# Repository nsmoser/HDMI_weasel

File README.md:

This board exists to switch between a pass-through HDMI signal and an HDMI signal generated from an RP2350A chip.
Note that this board does not contain HDMI connectors, but it does have FFC connectors for routing HDMI signals on/off board.
Has some DIP mechanical interfaces for working the chip, and an FFC connector w/ SPI & I2C pinned out for an add-on board.
Micro-SD card connector on the back to source images for the generated HDMI signal.

This was originally intended as a prank device (ex. take a screenshot of your neighbor's PC, load it on the SD card, and switch the input),
but it could also see use as a digital meeting or menu board on a single-input display where frequent switching between display on a loop and
a presentation from an external HDMI source.

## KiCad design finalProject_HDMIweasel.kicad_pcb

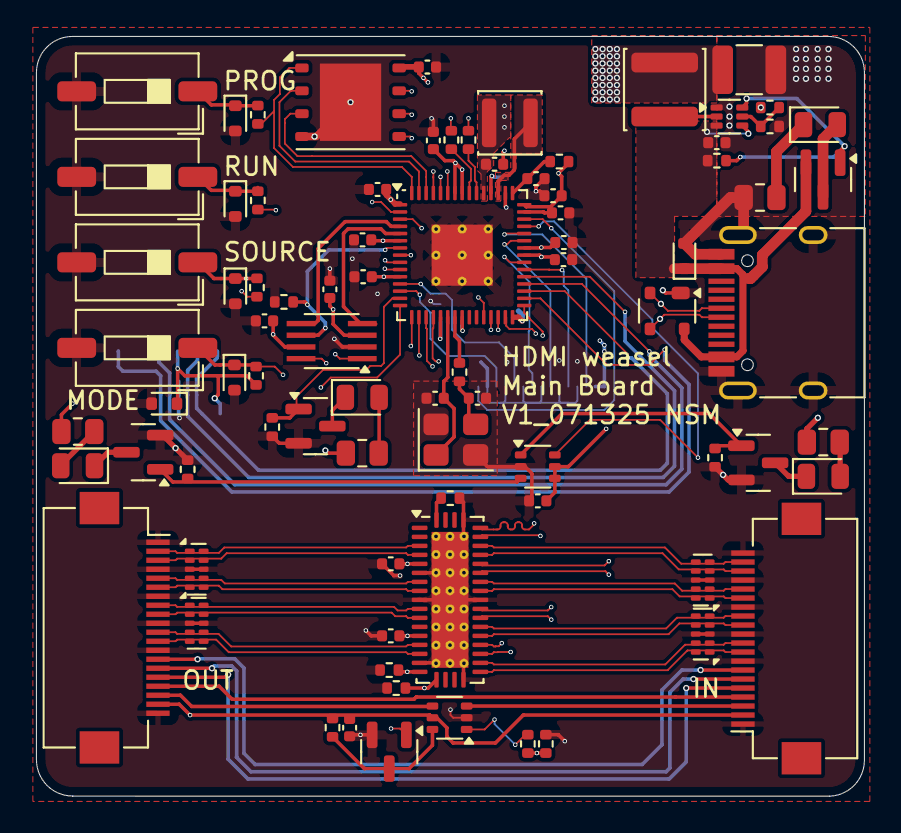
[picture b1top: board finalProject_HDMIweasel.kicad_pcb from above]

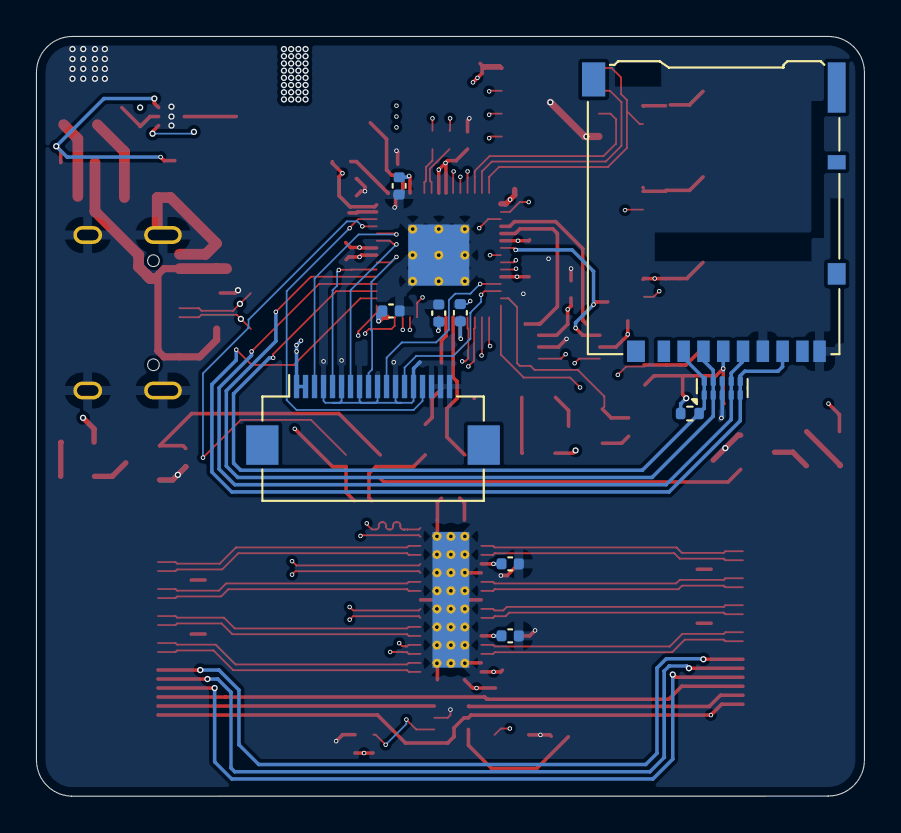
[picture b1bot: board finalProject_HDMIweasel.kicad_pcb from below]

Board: 6 copper layers, 46.0 x 42.2 mm, 93 parts (10 on the bottom side), 90 nets.

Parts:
C001, C201, C202, C203, C204, C205: 0.1u; C_0402_1005Metric
C101: 2.2u; C_0402_1005Metric
C102: 47u; C_1210_3225Metric
C301, C302, C303, C314: 4.7u; C_0402_1005Metric
C304, C305, C306, C307, C308, C309, C310, C311, C312, C313, C315, C318, C319: 100n; C_0402_1005Metric
C316, C317: 15p; C_0402_1005Metric
D001, D002, D003, D103: LED; LED_0805_2012Metric
D101: ESD5Z5V0; D_SOD-523
D102: PRTR5V0U2X; SOT-143
D301, D302, D303, D304, D305: ESD5Z3V3; D_SOD-523
J001: Conn_01x18_Pin; Hirose_FH12-18S-0.5SH_1x18-1MP_P0.50mm_Horizontal
J201, J202: Conn_01x20_Pin; Hirose_FH12-20S-0.5SH_1x20-1MP_P0.50mm_Horizontal
J301: Micro_SD_Card; microSD_HC_Hirose_DM3AT-SF-PEJM5
L101: 1u; L_Sunlord_SWPA4030S
L301: 3.3u; L_Sunlord_SWPA3015S
P101: USB_C_Plug_USB2.0; USB_C_Receptacle_HRO_TYPE-C-31-M-12
Q001, Q002, Q003, Q201: BSS138; SOT-23
Q101: BSS83P; SOT-23
R001, R003, R005, R102, R103, R204, R309, R310: 100k; R_0402_1005Metric
R002: 22; R_0805_2012Metric
R004, R006: 42.2; R_0805_2012Metric
R101: 453k; R_0402_1005Metric
R104: 188; R_0805_2012Metric
R201, R202, R203, R305, R306, R311: 10k; R_0402_1005Metric
R301, R302: 27; R_0402_1005Metric
R303, R304: 1k; R_0402_1005Metric
R307, R308: 100K; R_0402_1005Metric
R312: 33; R_0402_1005Metric
SW301, SW302, SW304, SW305: SW_DIP_x01; SW_DIP_SPSTx01_Slide_6.7x4.1mm_W6.73mm_P2.54mm_LowProfile_J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
U001, U206: TS5A3159ADCK; SOT-363_SC-70-6
U101: TPS62A02ADRL; SOT-563
U201: TMUXHS4412; WQFN-42-1EP_3.5x9mm_P0.5mm_EP2.05x7.55mm_ThermalVias
U202, U203, U204, U205, U304: TPD4E02B04DQA; USON-10_2.5x1.0mm_P0.5mm
U301: RP2350; QFN-60-1EP_7x7mm_P0.4mm_EP3.4x3.4mm_ThermalVias
U302: W25Q128JVP; WSON-8-1EP_6x5mm_P1.27mm_EP3.4x4.3mm
U303: TXS0102DCT; SSOP-8_2.95x2.8mm_P0.65mm
Y1: ABM8-22272-T3; Crystal_SMD_3225-4Pin_3.2x2.5mm

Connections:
+1V1: C302.1, C312.1, C313.1, C314.1, L301.1, U301.6 (DVDD), U301.23 (DVDD), U301.39 (DVDD), U301.50 (VREG_FB)
+3.3V: C001.1, C102.1, C201.1, C202.1, C203.1, C204.1, C303.1, C304.1, C305.1, C306.1, C307.1, C308.1, C309.1, C310.1, C311.1, C315.1, C319.1, D305.1 (K), J001.1, J001.2, J301.4 (VDD), L101.2, R002.1, R004.1, R006.1, R101.1, R309.1, R310.1, R311.2, R312.2, U001.4, U001.5 (V+), U201.5 (VCC), U201.13 (VCC), U301.1 (IOVDD), U301.11 (IOVDD), U301.20 (IOVDD), U301.30 (IOVDD), U301.38 (IOVDD), U301.44 (ADC_AVDD), U301.45 (IOVDD), U301.49 (VREG_VIN), U301.53 (USB_OTP_VDD), U301.54 (QSPI_IOVDD), U302.8 (VCC), U303.3 (VCCA)
/HDMI_switch/CEC: J201.14, J202.7, U301.15 (GPIO11)
/HDMI_switch/HDMI_IN_CK+: J202.19, U201.36 (DB0P), U205.5 (IO4)
/HDMI_switch/HDMI_IN_CK-: J202.18, U201.35 (DB0N), U205.4 (IO3)
/HDMI_switch/HDMI_IN_D0+: J202.16, U201.32 (DB1P), U205.2 (IO2)
/HDMI_switch/HDMI_IN_D0-: J202.15, U201.31 (DB1N), U205.1 (IO1)
/HDMI_switch/HDMI_IN_D1+: J202.13, U201.27 (DB2P), U204.5 (IO4)
/HDMI_switch/HDMI_IN_D1-: J202.12, U201.26 (DB2N), U204.4 (IO3)
/HDMI_switch/HDMI_IN_D2+: J202.10, U201.23 (DB3P), U204.2 (IO2)
/HDMI_switch/HDMI_IN_D2-: J202.9, U201.22 (DB3N), U204.1 (IO1)
/HDMI_switch/HDMI_OUT_CLK+: J201.2, U201.3 (D0P), U203.1 (IO1)
/HDMI_switch/HDMI_OUT_CLK-: J201.3, U201.4 (D0N), U203.2 (IO2)
/HDMI_switch/HDMI_OUT_D0+: J201.5, U201.7 (D1P), U203.4 (IO3)
/HDMI_switch/HDMI_OUT_D0-: J201.6, U201.8 (D1N), U203.5 (IO4)
/HDMI_switch/HDMI_OUT_D1+: J201.8, U201.10 (D2P), U202.1 (IO1)
/HDMI_switch/HDMI_OUT_D1-: J201.9, U201.11 (D2N), U202.2 (IO2)
/HDMI_switch/HDMI_OUT_D2+: J201.11, U201.14 (D3P), U202.4 (IO3)
/HDMI_switch/HDMI_OUT_D2-: J201.12, U201.15 (D3N), U202.5 (IO4)
/HDMI_switch/HOTPLUG_OUT: J201.18, U206.4
/HDMI_switch/PD: R201.1, U201.18 (PD), U301.3 (GPIO1)
/HDMI_switch/RPI_CLK+: U201.38 (DA0P), U301.18 (GPIO14)
/HDMI_switch/RPI_CLK-: U201.37 (DA0N), U301.19 (GPIO15)
/HDMI_switch/RPI_D0+: U201.34 (DA1P), U301.29 (GPIO18)
/HDMI_switch/RPI_D0-: U201.33 (DA1N), U301.31 (GPIO19)
/HDMI_switch/RPI_D1+: U201.29 (DA2P), U301.27 (GPIO16)
/HDMI_switch/RPI_D1-: U201.28 (DA2N), U301.28 (GPIO17)
/HDMI_switch/RPI_D2+: U201.25 (DA3P), U301.16 (GPIO12)
/HDMI_switch/RPI_D2-: U201.24 (DA3N), U301.17 (GPIO13)
/HDMI_switch/RPI_HOTPLUG: R307.2, U206.1
/HDMI_switch/SCL: J201.15, J202.6, U303.1 (B2)
/HDMI_switch/SDA: J201.16, J202.5, U303.8 (B1)
/HDMI_switch/SEL: Q201.1 (G), R202.1, U201.17 (SEL), U301.2 (GPIO0)
/HDMI_switch/V_HDMI: C205.1, C318.1, J201.19, J202.2, R204.1, U206.5 (V+), U303.7 (VCCB)
/HDMI_switch/hotplug: J202.3, U206.3
/HDMI_switch/util: J201.17, J202.4
/Microcontroller/HDMI_COMM_EN: R306.2, U301.7 (GPIO4), U303.6 (OE)
/Microcontroller/LED_HDMISOURCE: U001.6, U301.42 (GPIO28_ADC2)
/Microcontroller/LED_SYSACTIVE: Q001.1 (G), R001.1, U301.14 (GPIO10)
/Microcontroller/MANUAL_SWITCH: D303.1 (K), R309.2, SW304.1, U301.9 (GPIO6)
/Microcontroller/MODE_SWITCH: D304.1 (K), R310.2, SW305.1, U301.10 (GPIO7)
/Microcontroller/QSPI_SS: R303.2, U301.60 (QSPI_SS), U302.1 (~CS)
/Microcontroller/RPI_ADC (GPIO29): J001.15, U301.43 (GPIO29_ADC3)
/Microcontroller/RPI_SCL0 (GPIO9): J001.13, U301.13 (GPIO9)
/Microcontroller/RPI_SCL1: U301.5 (GPIO3), U303.4 (A2)
/Microcontroller/RPI_SDA0 (GPIO8): J001.11, U301.12 (GPIO8)
/Microcontroller/RPI_SDA1: U301.4 (GPIO2), U303.5 (A1)
/Microcontroller/RPI_SPI1_CS0 (GPIO25): J001.9, U301.37 (GPIO25)
/Microcontroller/RPI_SPI1_RX (GPIO24): J001.5, U301.36 (GPIO24)
/Microcontroller/RPI_SPI1_SCK (GPIO26): J001.7, U301.40 (GPIO26_ADC0)
/Microcontroller/RPI_SPI1_TX (GPIO27): J001.3, U301.41 (GPIO27_ADC1)
/Microcontroller/SPI0_CS0: J301.2 (DAT3/CD), R311.1, U301.33 (GPIO21), U304.1 (IO1)
/Microcontroller/SPI0_RX: J301.7 (DAT0), U301.32 (GPIO20), U304.5 (IO4)
/Microcontroller/SPI0_SCK: J301.5 (CLK), U301.34 (GPIO22), U304.4 (IO3)
/Microcontroller/SPI0_TX: J301.3 (CMD), U301.35 (GPIO23), U304.2 (IO2)
/Microcontroller/USB_D1N: R301.1, U301.51 (USB_DN)
/Microcontroller/USB_D1P: R302.1, U301.52 (USB_DP)
/Microcontroller/USB_DN: D102.2 (I/O1), P101.A7 (D-), R301.2
/Microcontroller/USB_DP: D102.3 (I/O2), P101.A6 (D+), R302.2
/Microcontroller/VREG_LX: L301.2, U301.48 (VREG_LX)
GND: C001.2, C101.2, C102.2, C201.2, C202.2, C203.2, C204.2, C205.2, C301.2, C302.2, C303.2, C304.2, C305.2, C306.2, C307.2, C308.2, C309.2, C310.2, C311.2, C312.2, C313.2, C314.2, C315.2, C316.2, C317.2, C318.2, C319.2, D101.2 (A), D102.1 (GND), D301.2 (A), D302.2 (A), D303.2 (A), D304.2 (A), D305.2 (A), J001.4, J001.6, J001.8, J001.10, J001.12, J001.14, J001.16, J001.17, J001.18, J201.1, J201.4, J201.7, J201.10, J201.13, J201.20, J202.1, J202.8, J202.11, J202.14, J202.17, J202.20, J301.6 (VSS), J301.9 (SHIELD), P101.A1 (GND), P101.A12 (GND), P101.B1 (GND), P101.B12 (GND), P101.S1 (SHIELD), Q001.2 (S), Q002.2 (S), Q003.2 (S), Q201.2 (S), R001.2, R003.2, R005.2, R102.2, R104.2, R201.2, R202.2, R203.1, R306.1, R308.2, SW301.2, SW302.2, SW304.2, SW305.2, U001.2 (GND), U101.1 (GND), U201.6 (GND), U201.9 (GND), U201.16 (GND), U201.21 (GND), U201.30 (GND), U201.39 (GND), U201.43 (GND), U202.3 (G), U202.8 (G), U203.3 (G), U203.8 (G), U204.3 (G), U204.8 (G), U205.3 (G), U205.8 (G), U206.2 (GND), U301.47 (VREG_PGND), U301.61 (GND), U302.4 (GND), U302.9 (EP), U303.2 (GND), U304.3 (G), U304.8 (G), Y1.2, Y1.4
unnamed: C316.1, R304.1, Y1.3
unnamed: D001.2 (A), R002.2
unnamed: D001.1 (K), Q001.3 (D)
unnamed: D002.2 (A), R004.2
unnamed: D002.1 (K), Q002.3 (D)
unnamed: D003.2 (A), R006.2
unnamed: D003.1 (K), Q003.3 (D)
unnamed: D103.2 (A), Q101.3 (D)
unnamed: D103.1 (K), R104.1
unnamed: D301.1 (K), R303.1, SW301.1
unnamed: D302.1 (K), R305.1, SW302.1
unnamed: Q002.1 (G), R003.1, U001.3
unnamed: Q003.1 (G), R005.1, U001.1
unnamed: Q101.1 (G), R103.2, U101.6 (PG)
unnamed: Q201.3 (D), R204.2, U206.6
unnamed: R101.2, R102.1, U101.5 (FB)
unnamed: L101.1, U101.2 (SW)
unnamed: R203.2, U201.42 (RSVD)
unnamed: R307.1, R308.1, U301.8 (GPIO5)
unnamed: U301.56 (QSPI_SCLK), U302.6 (CLK)
unnamed: U301.57 (QSPI_SD0), U302.5 (DI/IO_{0})
unnamed: U301.59 (QSPI_SD1), U302.2 (DO/IO_{1})
unnamed: U301.58 (QSPI_SD2), U302.3 (~WP/IO_{2})
unnamed: U301.55 (QSPI_SD3), U302.7 (~HOLD/~RESET/IO_{3})
unnamed: R305.2, U301.26 (RUN)
unnamed: C301.1, R312.1, U301.46 (VREG_AVDD)
unnamed: C317.1, U301.21 (XIN), Y1.1
unnamed: R304.2, U301.22 (XOUT)
VBUS: C101.1, D101.1 (K), D102.4 (VCC), P101.A4 (VBUS), P101.A9 (VBUS), P101.B4 (VBUS), P101.B9 (VBUS), Q101.2 (S), R103.1, U101.3 (VIN), U101.4 (EN)

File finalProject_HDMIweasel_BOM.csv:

Comment,Designator,Footprint,JLCPCB Part #
0.1u,"C001,C201,C202,C203,C204,C205",Capacitor_SMD:C_0402_1005Metric,C71629
2.2u,C101,Capacitor_SMD:C_0402_1005Metric,C237392
47u,C102,Capacitor_SMD:C_1210_3225Metric,C84494
4.7u,"C301,C302,C303,C314",Capacitor_SMD:C_0402_1005Metric,"C71633,C77004"
100n,"C304,C305,C306,C307,C308,C309,C310,C311,C312,C313,C315,C318,C319",Capacitor_SMD:C_0402_1005Metric,C71629
15p,"C316,C317",Capacitor_SMD:C_0402_1005Metric,C76950
LED,"D002,D003",LED_SMD:LED_0805_2012Metric,C7496841
LED,D001,LED_SMD:LED_0805_2012Metric,C84260
LED,D103,LED_SMD:LED_0805_2012Metric,C84262
ESD5Z5V0,D101,Diode_SMD:D_SOD-523,C248788
PRTR5V0U2X,D102,Package_TO_SOT_SMD:SOT-143,C12333
ESD5Z3V3,"D301,D302,D303,D304,D305",Diode_SMD:D_SOD-523,C502545
Conn_01x18_Pin,J001,Connector_FFC-FPC:Hirose_FH12-18S-0.5SH_1x18-1MP_P0.50mm_Horizontal,C506792
Conn_01x20_Pin,"J201,J202",Connector_FFC-FPC:Hirose_FH12-20S-0.5SH_1x20-1MP_P0.50mm_Horizontal,C596730
Micro_SD_Card,J301,Connector_Card:microSD_HC_Hirose_DM3AT-SF-PEJM5,C114218
1u,L101,Inductor_SMD:L_Sunlord_SWPA4030S,C42193
3.3u,L301,Inductor_SMD:L_Sunlord_SWPA3015S,C48020
USB_C_Plug_USB2.0,P101,Connector_USB:USB_C_Receptacle_HRO_TYPE-C-31-M-12,C165948
BSS138,"Q001,Q002,Q003,Q201",Package_TO_SOT_SMD:SOT-23,C24553
BSS83P,Q101,Package_TO_SOT_SMD:SOT-23,C2932927
100k,"R001,R003,R005,R102,R103,R204,R309,R310",Resistor_SMD:R_0402_1005Metric,C481918
22,R002,Resistor_SMD:R_0805_2012Metric,C17561
42.2,"R004,R006",Resistor_SMD:R_0805_2012Metric,C410018
453k,R101,Resistor_SMD:R_0402_1005Metric,C843903
188,R104,Resistor_SMD:R_0805_2012Metric,C104054
10k,"R201,R202,R203,R305,R306,R311",Resistor_SMD:R_0402_1005Metric,C71617
27,"R301,R302",Resistor_SMD:R_0402_1005Metric,C138021
1k,"R303,R304",Resistor_SMD:R_0402_1005Metric,C163485
100K,"R307,R308",Resistor_SMD:R_0402_1005Metric,C481918
33,R312,Resistor_SMD:R_0402_1005Metric,C25105
SW_DIP_x01,"SW301,SW302,SW304,SW305",Button_Switch_SMD:SW_DIP_SPSTx01_Slide_6.7x4.1mm_W6.73mm_P2.54mm_LowProfile_JPin,C2884835
TS5A3159ADCK,"U001,U206",Package_TO_SOT_SMD:SOT-363_SC-70-6,C475493
TPS62A02ADRL,U101,Package_TO_SOT_SMD:SOT-563,C5820994
TMUXHS4412,U201,Package_DFN_QFN:WQFN-42-1EP_3.5x9mm_P0.5mm_EP2.05x7.55mm_ThermalVias,C3657223
TPD4E02B04DQA,"U202,U203,U204,U205,U304",Package_SON:USON-10_2.5x1.0mm_P0.5mm,C106794
RP2350,U301,Package_DFN_QFN:QFN-60-1EP_7x7mm_P0.4mm_EP3.4x3.4mm_ThermalVias,C42411118
W25Q128JVP,U302,Package_SON:WSON-8-1EP_6x5mm_P1.27mm_EP3.4x4.3mm,C190862
TXS0102DCT,U303,Package_SO:SSOP-8_2.95x2.8mm_P0.65mm,C324082
ABM8-22272-T3,Y1,Crystal:Crystal_SMD_3225-4Pin_3.2x2.5mm,C20625731

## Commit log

2025-07-26 Initial upload
